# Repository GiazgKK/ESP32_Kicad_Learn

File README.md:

# ESP32-WROOM-32E Learning Board

A four-layer ESP32 development board designed in **KiCad 10** as a practical learning project. The board combines USB-C power and programming, automatic boot control, environmental sensing, motion sensing, GPIO expansion, and a PCB antenna-aware layout.

## Project Goals

This project was created to learn and practice:

- Schematic capture and electrical rule checking
- Component selection and footprint management
- Four-layer PCB stack-up planning
- Component placement and signal routing
- USB 2.0 Full-Speed routing and ESD protection
- Ground planes, copper pours, and stitching vias
- ESP32 boot-strapping and automatic programming circuits
- RF antenna placement and copper keepout design
- Design rule checking and manufacturing preparation

## Hardware Overview

The board is built around an **ESP32-WROOM-32E** Wi-Fi and Bluetooth module and includes:

- USB-C connector for 5 V power and programming
- TPD2EUSB30A protection for the USB data lines
- CH340C USB-to-UART converter
- Automatic reset and boot circuit using DTR/RTS
- TLV75733 3.3 V linear regulator
- BME280 temperature, humidity, and pressure sensor over SPI
- MPU-6050 six-axis accelerometer and gyroscope over I2C
- RESET and BOOT push buttons
- User and power indicator LEDs
- GPIO headers and test points for power, UART, EN, and BOOT

## Schematic Design

The schematic is separated into functional blocks for easier review and debugging. It includes USB-C input and protection, power regulation, USB-to-UART conversion, ESP32 boot control, sensors, GPIO headers, and test points.

Important design details include:

- Separate 5.1 kΩ pull-down resistors on USB-C CC1 and CC2
- ESD protection placed on the USB D+ and D− signals
- 10 kΩ pull-ups on ESP32 EN and GPIO0
- Local decoupling capacitors close to each IC
- I2C pull-ups for the MPU-6050 interface
- Clearly identified ESP32 strapping pins on the schematic
- Test points for the main power and programming signals

## PCB Layout

The PCB uses the following four-layer structure:

| Layer | Purpose |
|---|---|
| `F.Cu` | Components, primary signal routing, and GND copper pour |
| `In1.Cu` | Continuous GND reference plane |
| `In2.Cu` | 3.3 V power plane |
| `B.Cu` | Secondary routing and GND copper pour |

The routing view below shows component placement, signal fan-out, vias, and the ESP32 module before the outer-layer copper fills are emphasized.

## Grounding and Power Distribution

Ground pours are used on both outer copper layers and connected to the internal GND plane with stitching vias. The internal ground plane provides a short return path beneath signal traces, while the internal 3.3 V plane distributes power across the board.

The filled-zone view also highlights several layout decisions:

- GND stitching vias connect the outer pours to the internal ground plane
- Copper islands are removed when they cannot connect reliably to GND
- USB and IC ground connections have short paths to the reference plane
- The ESP32 antenna area is kept free of copper, tracks, pads, and vias
- The module antenna extends beyond the carrier-board edge to reduce RF interference

## ESP32 Antenna Placement

The ESP32-WROOM-32E is positioned at the edge of the carrier PCB. The antenna section extends beyond the `Edge.Cuts` boundary, and a multilayer keepout prevents copper and routing from entering the antenna region.

This placement is intended to reduce detuning caused by the carrier PCB and nearby copper. The final enclosure should also keep metal, wiring, and batteries away from the antenna.

## 3D Preview

The 3D rendering at the top of this README is used to review component orientation, connector access, silkscreen readability, and the ESP32 antenna overhang. It also provides a quick mechanical check before generating manufacturing files or designing an enclosure.

## Current Status

This is an educational work in progress. The main schematic and PCB routing are complete, and the design currently includes:

- A project-specific ESP32 footprint with antenna keepout rules
- 0.3 mm thermal-via drills under the ESP32 exposed GND pad
- Outer-layer GND pours and GND stitching vias
- Dedicated internal GND and 3.3 V planes
- USB-C, USB-to-UART, automatic programming, and sensor interfaces

Before manufacturing, the design still needs a final ERC/DRC pass, verification against the selected PCB manufacturer's four-layer stack-up, and a final Gerber and drill-file review.

## Repository Structure

```text
.
|-- ESP32_Wroom_Learn.kicad_pro   # KiCad project settings
|-- ESP32_Wroom_Learn.kicad_sch   # Main schematic
|-- ESP32_Wroom_Learn.kicad_pcb   # Four-layer PCB layout
|-- ESP32_Wroom_Learn.pretty/     # Project-specific footprints
|-- fp-lib-table                   # Project footprint-library table
|-- libraries/                    # Project-specific library resources
`-- docs/images/                  # README screenshots
```

## Requirements

- KiCad 10 or later

Open `ESP32_Wroom_Learn.kicad_pro` from the KiCad Project Manager to load the schematic, PCB, and project-specific libraries.

## Learning Notes

Some of the most useful lessons from this project were:

1. A clean schematic structure makes layout and debugging much easier.
2. A continuous reference plane is more important than forcing copper into every small gap on an outer layer.
3. Copper pours must be refilled and checked after changing the board outline or keepout regions.
4. Stitching vias are useful only when they are assigned to GND and connect otherwise separated ground regions.
5. ESP32 antenna placement must be considered before finalizing the board outline and component placement.
6. Custom footprints should be stored in the project library instead of modifying KiCad's system libraries.
7. ERC and DRC reports must be regenerated after the latest design changes rather than relying on old reports.

## License

No license has been selected yet. Unless a license is added, the design is publicly viewable but is not automatically licensed for reuse or redistribution.

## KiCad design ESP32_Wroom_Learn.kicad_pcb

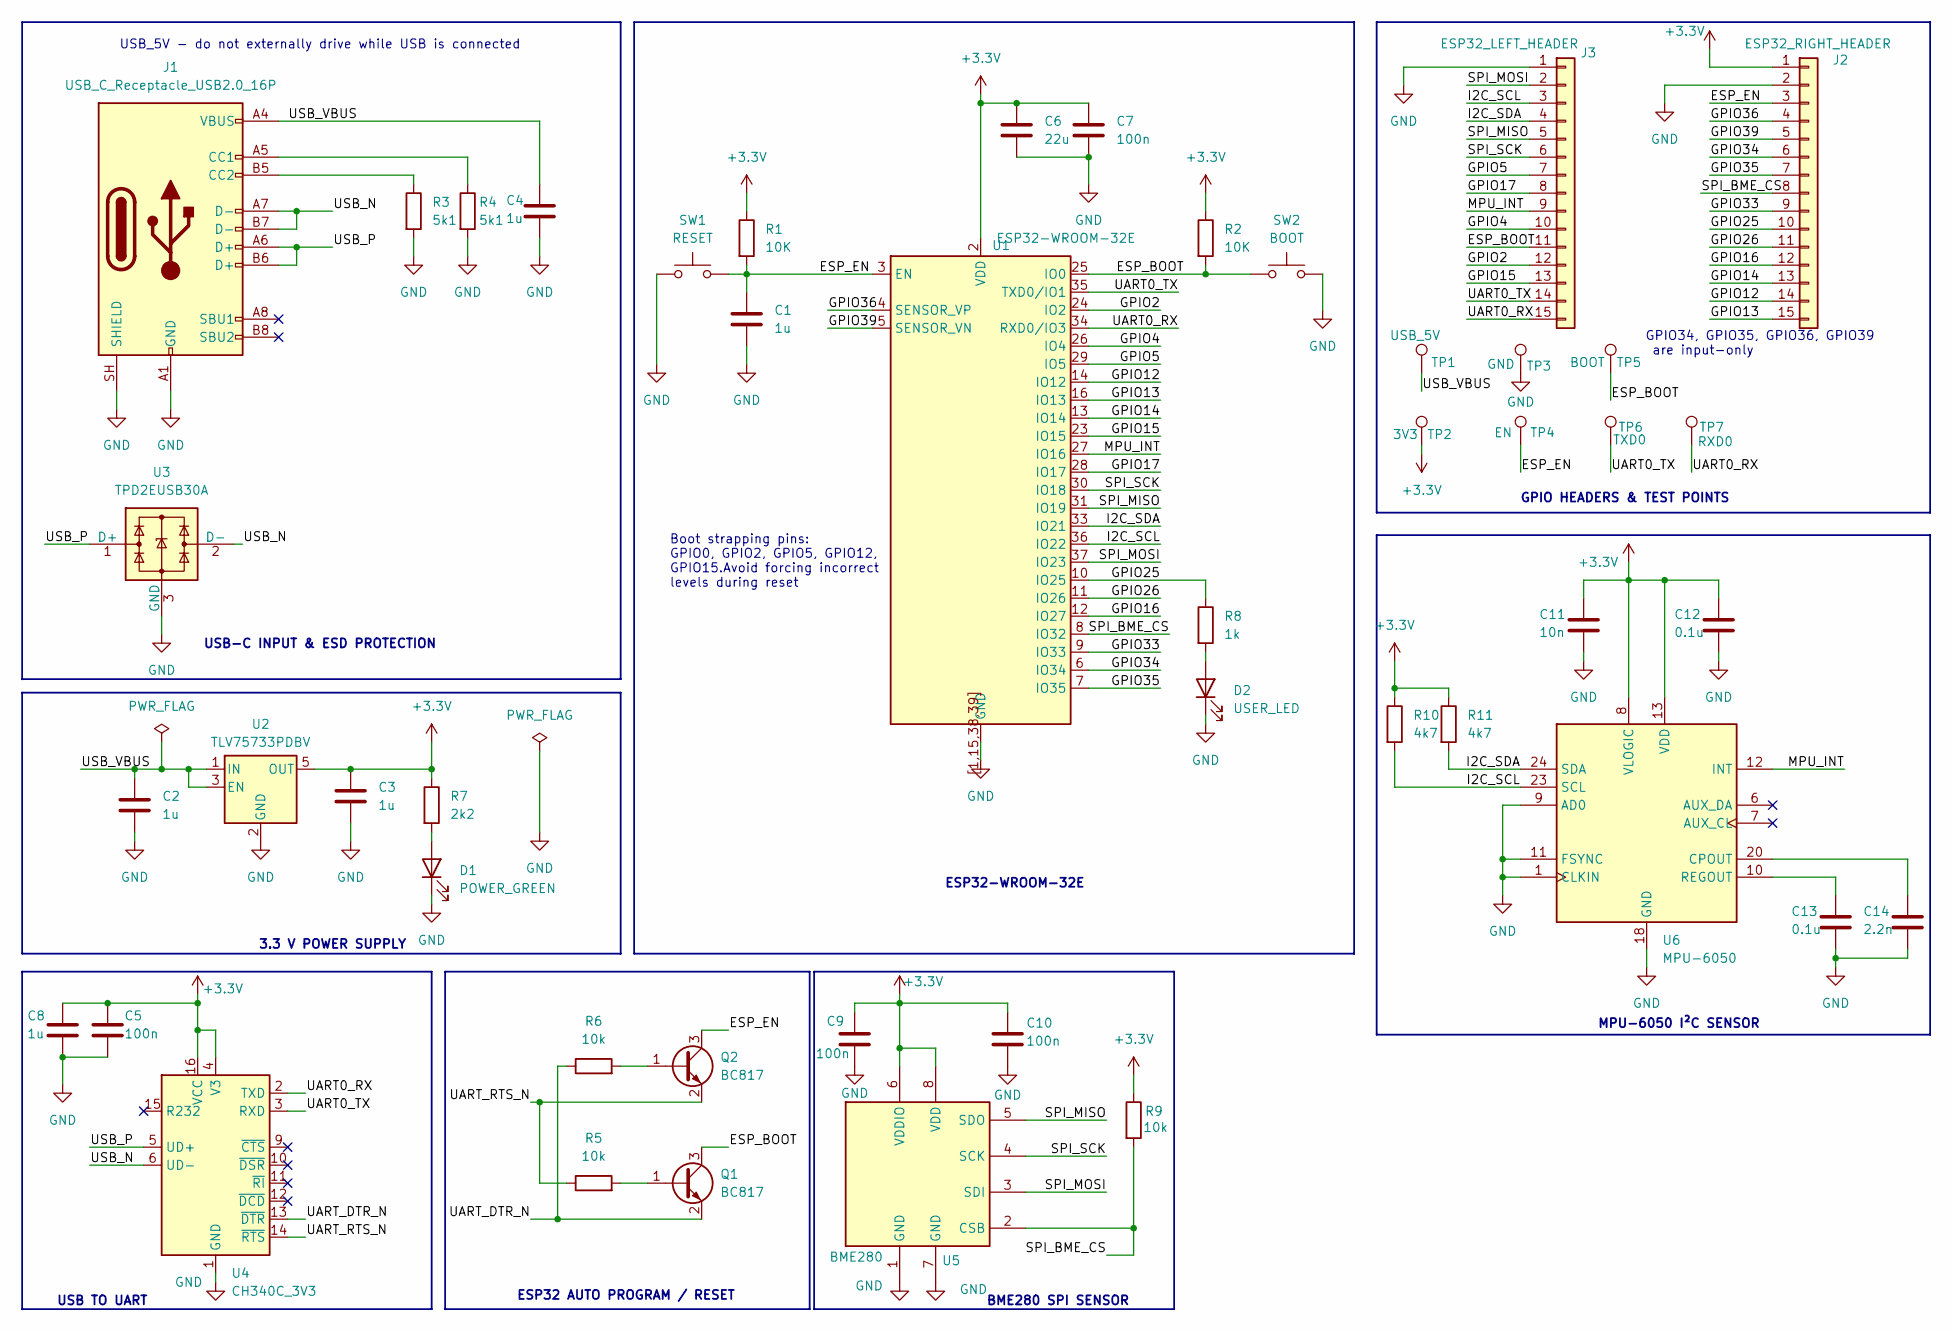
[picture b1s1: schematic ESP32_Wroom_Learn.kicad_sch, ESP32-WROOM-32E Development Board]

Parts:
C1, C2, C3, C4, C8: 1u; C_0805_2012Metric_Pad1.18x1.45mm_HandSolder
C5: 100n; C_0805_2012Metric_Pad1.18x1.45mm_HandSolder
C6: 22u; C_1206_3216Metric_Pad1.33x1.80mm_HandSolder
C7, C9, C10: 100n; C_0603_1608Metric_Pad1.08x0.95mm_HandSolder
C11: 10n; C_0603_1608Metric_Pad1.08x0.95mm_HandSolder
C12, C13: 0.1u; C_0603_1608Metric_Pad1.08x0.95mm_HandSolder
C14: 2.2n; C_0603_1608Metric_Pad1.08x0.95mm_HandSolder
D1: POWER_GREEN; LED_0603_1608Metric_Pad1.05x0.95mm_HandSolder
D2: USER_LED; LED_0603_1608Metric_Pad1.05x0.95mm_HandSolder
J1: USB_C_Receptacle_USB2.0_16P; USB_C_Receptacle_GCT_USB4105-xx-A_16P_TopMnt_Horizontal
J2: ESP32_RIGHT_HEADER; PinHeader_1x15_P2.54mm_Vertical
J3: ESP32_LEFT_HEADER; PinHeader_1x15_P2.54mm_Vertical
Q1, Q2: BC817; SOT-23
R1, R2: 10K; R_0603_1608Metric_Pad0.98x0.95mm_HandSolder
R3, R4: 5k1; R_0603_1608Metric_Pad0.98x0.95mm_HandSolder
R5, R6, R9: 10k; R_0603_1608Metric_Pad0.98x0.95mm_HandSolder
R7: 2k2; R_0603_1608Metric_Pad0.98x0.95mm_HandSolder
R8: 1k; R_0603_1608Metric_Pad0.98x0.95mm_HandSolder
R10, R11: 4k7; R_0603_1608Metric_Pad0.98x0.95mm_HandSolder
SW1: RESET; SW_Push_1P1T_NO_CK_KMR2
SW2: BOOT; SW_Push_1P1T_NO_CK_KMR2
TP1: USB_5V; TestPoint_THTPad_D1.5mm_Drill0.7mm
TP2: 3V3; TestPoint_THTPad_D1.5mm_Drill0.7mm
TP3: GND; TestPoint_THTPad_D1.5mm_Drill0.7mm
TP4: EN; TestPoint_THTPad_D1.5mm_Drill0.7mm
TP5: BOOT; TestPoint_THTPad_D1.5mm_Drill0.7mm
TP6: TXD0; TestPoint_THTPad_D1.5mm_Drill0.7mm
TP7: RXD0; TestPoint_THTPad_D1.5mm_Drill0.7mm
U1: ESP32-WROOM-32E; ESP32-WROOM-32E_Custom
U2: TLV75733PDBV; SOT-23-5
U3: TPD2EUSB30A; Texas_DRT-3
U4: CH340C_3V3; SOIC-16_3.9x9.9mm_P1.27mm
U5: BME280; Bosch_LGA-8_2.5x2.5mm_P0.65mm_ClockwisePinNumbering
U6: MPU-6050; InvenSense_QFN-24_4x4mm_P0.5mm

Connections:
+3.3V: C3.1, C5.1, C6.1, C7.1, C8.1, C9.1, C10.1, C11.1, C12.1, J2.1, R1.1, R2.1, R7.1, R9.1, R10.1, R11.1, TP2.1 (1_1), U1.2 (VDD), U2.5 (OUT), U4.4 (V3), U4.16 (VCC), U5.6 (VDDIO), U5.8 (VDD), U6.8 (VLOGIC), U6.13 (VDD)
/ESP_BOOT: J3.11, Q1.3 (C), R2.2, SW2.1, TP5.1 (1_1), U1.25 (IO0)
/ESP_EN: C1.1, J2.3, Q2.3 (C), R1.2, SW1.2, TP4.1 (1_1), U1.3 (EN)
/GPIO2: J3.12, U1.24 (IO2)
/GPIO4: J3.10, U1.26 (IO4)
/GPIO5: J3.7, U1.29 (IO5)
/GPIO12: J2.14, U1.14 (IO12)
/GPIO13: J2.15, U1.16 (IO13)
/GPIO14: J2.13, U1.13 (IO14)
/GPIO15: J3.13, U1.23 (IO15)
/GPIO16: J2.12, U1.12 (IO27)
/GPIO17: J3.8, U1.28 (IO17)
/GPIO25: J2.10, R8.1, U1.10 (IO25)
/GPIO26: J2.11, U1.11 (IO26)
/GPIO33: J2.9, U1.9 (IO33)
/GPIO34: J2.6, U1.6 (IO34)
/GPIO35: J2.7, U1.7 (IO35)
/GPIO36: J2.4, U1.4 (SENSOR_VP)
/GPIO39: J2.5, U1.5 (SENSOR_VN)
/I2C_SCL: J3.3, R10.2, U1.36 (IO22), U6.23 (SCL)
/I2C_SDA: J3.4, R11.2, U1.33 (IO21), U6.24 (SDA)
/MPU_INT: J3.9, U1.27 (IO16), U6.12 (INT)
/SPI_BME_CS: J2.8, R9.2, U1.8 (IO32), U5.2 (CSB)
/SPI_MISO: J3.5, U1.31 (IO19), U5.5 (SDO)
/SPI_MOSI: J3.2, U1.37 (IO23), U5.3 (SDI)
/SPI_SCK: J3.6, U1.30 (IO18), U5.4 (SCK)
/UART0_RX: J3.15, TP7.1 (1_1), U1.34 (RXD0/IO3), U4.2 (TXD)
/UART0_TX: J3.14, TP6.1 (1_1), U1.35 (TXD0/IO1), U4.3 (RXD)
/UART_DTR_N: Q1.2 (E), R6.1, U4.13 (~DTR)
/UART_RTS_N: Q2.2 (E), R5.1, U4.14 (~RTS)
/USB_N: J1.A7 (D-), J1.B7 (D-), U3.2 (D-), U4.6 (UD-)
/USB_P: J1.A6 (D+), J1.B6 (D+), U3.1 (D+), U4.5 (UD+)
/USB_VBUS: C2.1, C4.1, J1.A4 (VBUS), J1.A9 (VBUS), J1.B4 (VBUS), J1.B9 (VBUS), TP1.1 (1_1), U2.1 (IN), U2.3 (EN)
GND: C1.2, C2.2, C3.2, C4.2, C5.2, C6.2, C7.2, C8.2, C9.2, C10.2, C11.2, C12.2, C13.2, C14.2, D1.1 (K), D2.1 (K), J1.A1 (GND), J1.A12 (GND), J1.B1 (GND), J1.B12 (GND), J1.SH (SHIELD), J2.2, J3.1, R3.2, R4.2, SW1.1, SW2.2, TP3.1 (1_1), U1.1 (GND), U1.15 (GND), U1.38 (GND), U1.39 (GND), U1.[1,15,38,39] (GND), U2.2 (GND), U3.3 (GND), U4.1 (GND), U5.1 (GND), U5.7 (GND), U6.1 (CLKIN), U6.9 (AD0), U6.11 (FSYNC), U6.18 (GND); also elsewhere on the board
unnamed: D1.2 (A), R7.2
unnamed: D2.2 (A), R8.2
unnamed: J1.A5 (CC1), R4.1
unnamed: J1.B5 (CC2), R3.1
unnamed: Q1.1 (B), R5.2
unnamed: Q2.1 (B), R6.2
unnamed: C14.1, U6.20 (CPOUT)
unnamed: C13.1, U6.10 (REGOUT)

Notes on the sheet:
MPU-6050 I²C SENSOR
BME280 SPI SENSOR
USB-C INPUT & ESD PROTECTION
USB TO UART
3.3 V POWER SUPPLY
ESP32-WROOM-32E
USB_5V - do not externally drive while USB is connected
Boot strapping pins: GPIO0, GPIO2, GPIO5, GPIO12, GPIO15.Avoid forcing incorrect levels during reset
GPIO34, GPIO35, GPIO36, GPIO39 are input-only
ESP32 AUTO PROGRAM / RESET
GPIO HEADERS & TEST POINTS

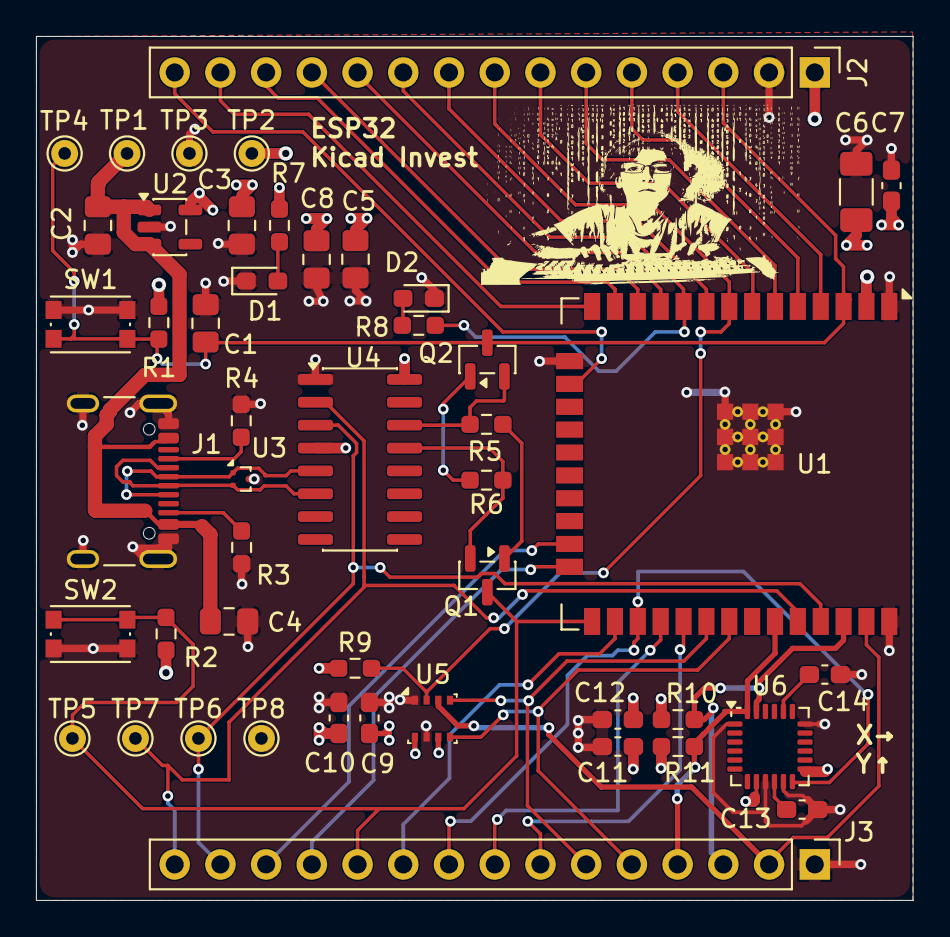
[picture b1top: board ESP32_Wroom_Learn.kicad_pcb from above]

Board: 4 copper layers, 48.7 x 48.0 mm, 48 parts (0 on the bottom side), 42 nets.

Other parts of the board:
TP8: GND; TestPoint_THTPad_D1.5mm_Drill0.7mm

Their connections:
GND: TP8.1 (1_1); also elsewhere on the board
